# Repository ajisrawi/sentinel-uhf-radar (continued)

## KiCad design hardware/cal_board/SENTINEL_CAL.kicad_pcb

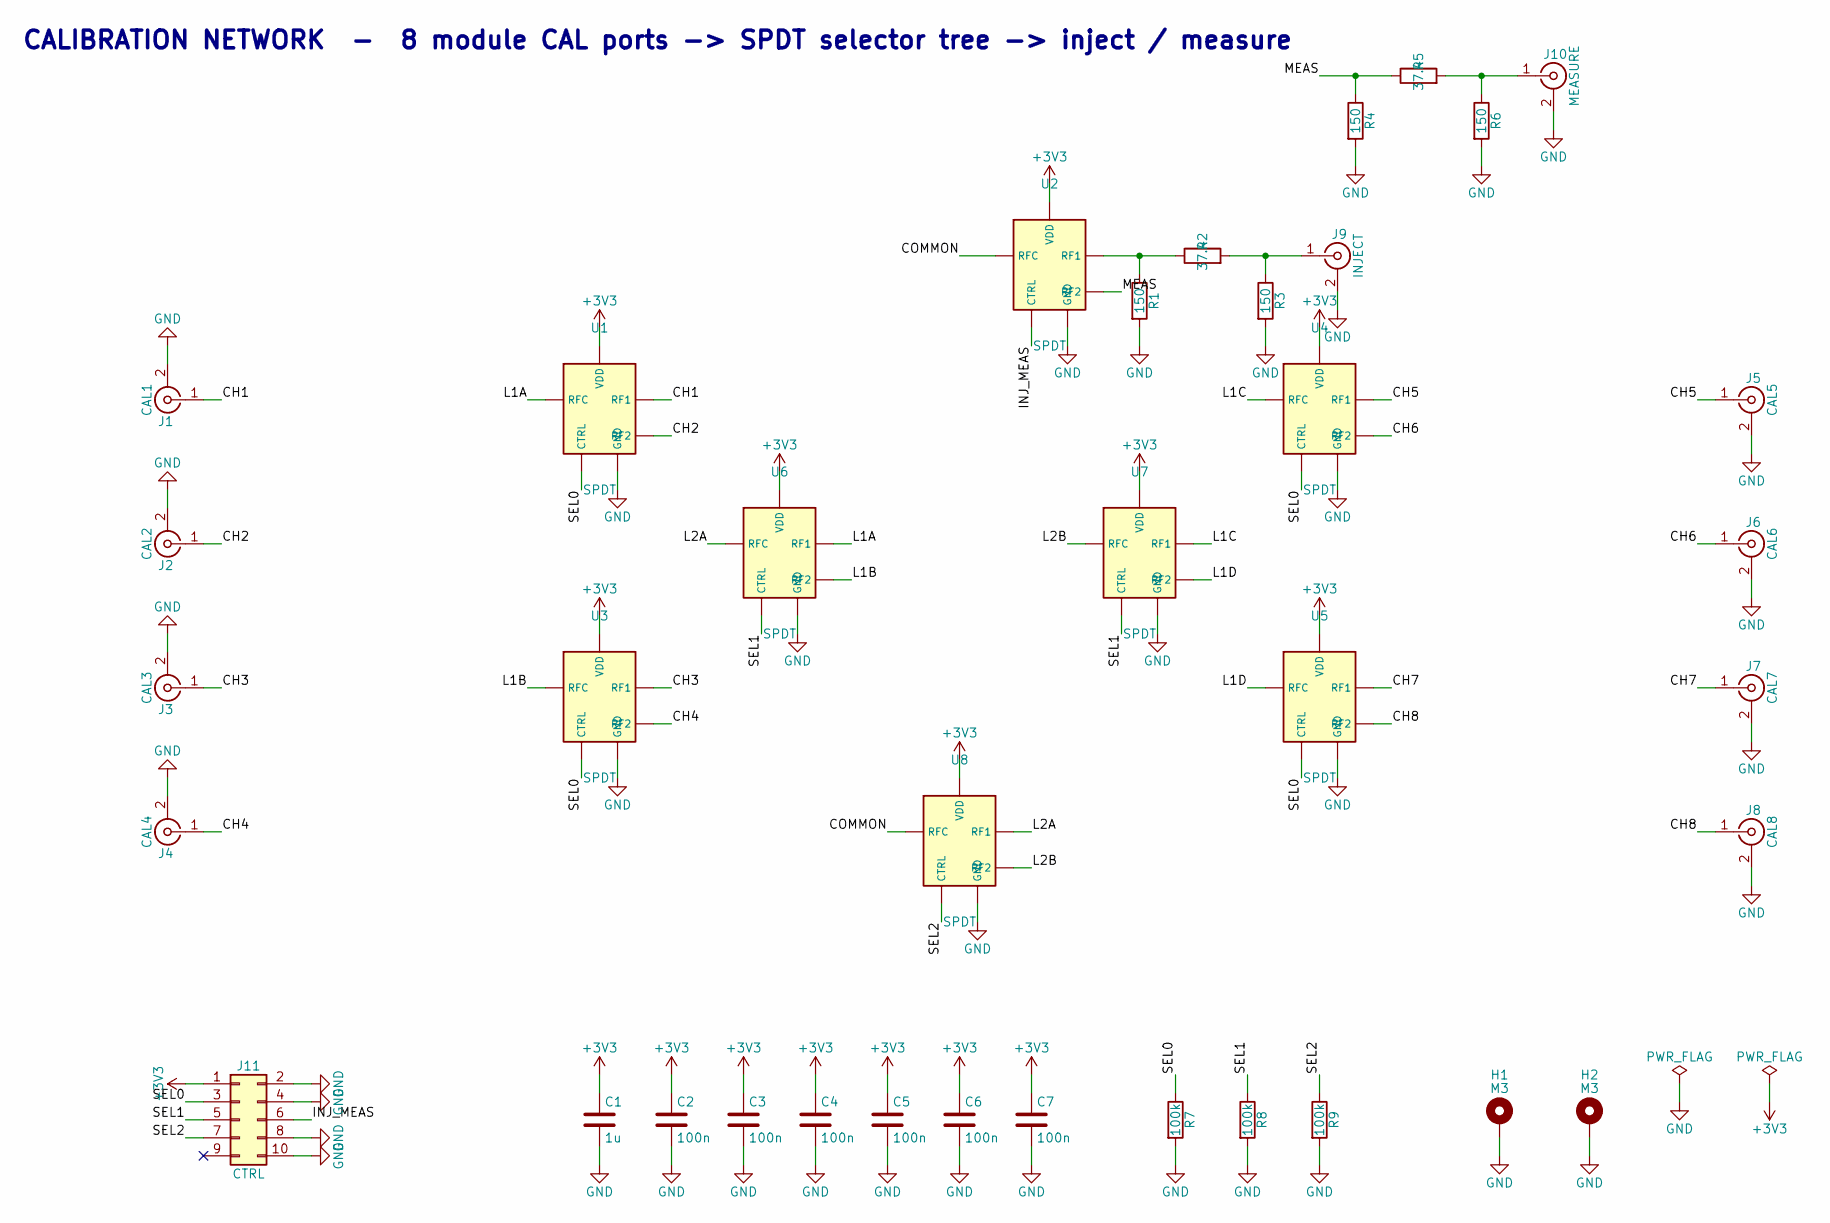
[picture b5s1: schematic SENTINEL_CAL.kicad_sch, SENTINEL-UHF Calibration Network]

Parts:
C1: 1u; C_0603_1608Metric
C2, C3, C4, C5, C6, C7: 100n; C_0603_1608Metric
H1, H2: M3; MountingHole_3.2mm_M3_Pad
J1: CAL1; SMA_Amphenol_132289_EdgeMount
J2: CAL2; SMA_Amphenol_132289_EdgeMount
J3: CAL3; SMA_Amphenol_132289_EdgeMount
J4: CAL4; SMA_Amphenol_132289_EdgeMount
J5: CAL5; SMA_Amphenol_132289_EdgeMount
J6: CAL6; SMA_Amphenol_132289_EdgeMount
J7: CAL7; SMA_Amphenol_132289_EdgeMount
J8: CAL8; SMA_Amphenol_132289_EdgeMount
J9: INJECT; SMA_Amphenol_132289_EdgeMount
J10: MEASURE; SMA_Amphenol_132289_EdgeMount
J11: CTRL; PinHeader_2x05_P2.54mm_Vertical
R1, R3, R4, R6: 150; R_0603_1608Metric
R2, R5: 37.4; R_0603_1608Metric
R7, R8, R9: 100k; R_0603_1608Metric
U1, U2, U3, U4, U5, U6, U7, U8: SPDT; SOT-363_SC-70-6

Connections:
+3V3: C1.1, C2.1, C3.1, C4.1, C5.1, C6.1, C7.1, J11.1, U1.6 (VDD), U2.6 (VDD), U3.6 (VDD), U4.6 (VDD), U5.6 (VDD), U6.6 (VDD), U7.6 (VDD), U8.6 (VDD)
CH1: J1.1 (In), U1.1 (RF1)
CH2: J2.1 (In), U1.3 (RF2)
CH3: J3.1 (In), U3.1 (RF1)
CH4: J4.1 (In), U3.3 (RF2)
CH5: J5.1 (In), U4.1 (RF1)
CH6: J6.1 (In), U4.3 (RF2)
CH7: J7.1 (In), U5.1 (RF1)
CH8: J8.1 (In), U5.3 (RF2)
COMMON: U2.5 (RFC), U8.5 (RFC)
GND: C1.2, C2.2, C3.2, C4.2, C5.2, C6.2, C7.2, H1.1, H2.1, J1.2 (Ext), J2.2 (Ext), J3.2 (Ext), J4.2 (Ext), J5.2 (Ext), J6.2 (Ext), J7.2 (Ext), J8.2 (Ext), J9.2 (Ext), J10.2 (Ext), J11.2, J11.4, J11.8, J11.10, R1.2, R3.2, R4.2, R6.2, R7.2, R8.2, R9.2, U1.2 (GND), U2.2 (GND), U3.2 (GND), U4.2 (GND), U5.2 (GND), U6.2 (GND), U7.2 (GND), U8.2 (GND)
INJ_MEAS: J11.6, U2.4 (CTRL)
L1A: U1.5 (RFC), U6.1 (RF1)
L1B: U3.5 (RFC), U6.3 (RF2)
L1C: U4.5 (RFC), U7.1 (RF1)
L1D: U5.5 (RFC), U7.3 (RF2)
L2A: U6.5 (RFC), U8.1 (RF1)
L2B: U7.5 (RFC), U8.3 (RF2)
MEAS: R4.1, R5.1, U2.3 (RF2)
unnamed: J9.1 (In), R2.2, R3.1
unnamed: J10.1 (In), R5.2, R6.1
unnamed: R1.1, R2.1, U2.1 (RF1)
SEL0: J11.3, R7.1, U1.4 (CTRL), U3.4 (CTRL), U4.4 (CTRL), U5.4 (CTRL)
SEL1: J11.5, R8.1, U6.4 (CTRL), U7.4 (CTRL)
SEL2: J11.7, R9.1, U8.4 (CTRL)

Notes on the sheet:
CALIBRATION NETWORK - 8 module CAL ports -> SPDT selector tree -> inject / measure

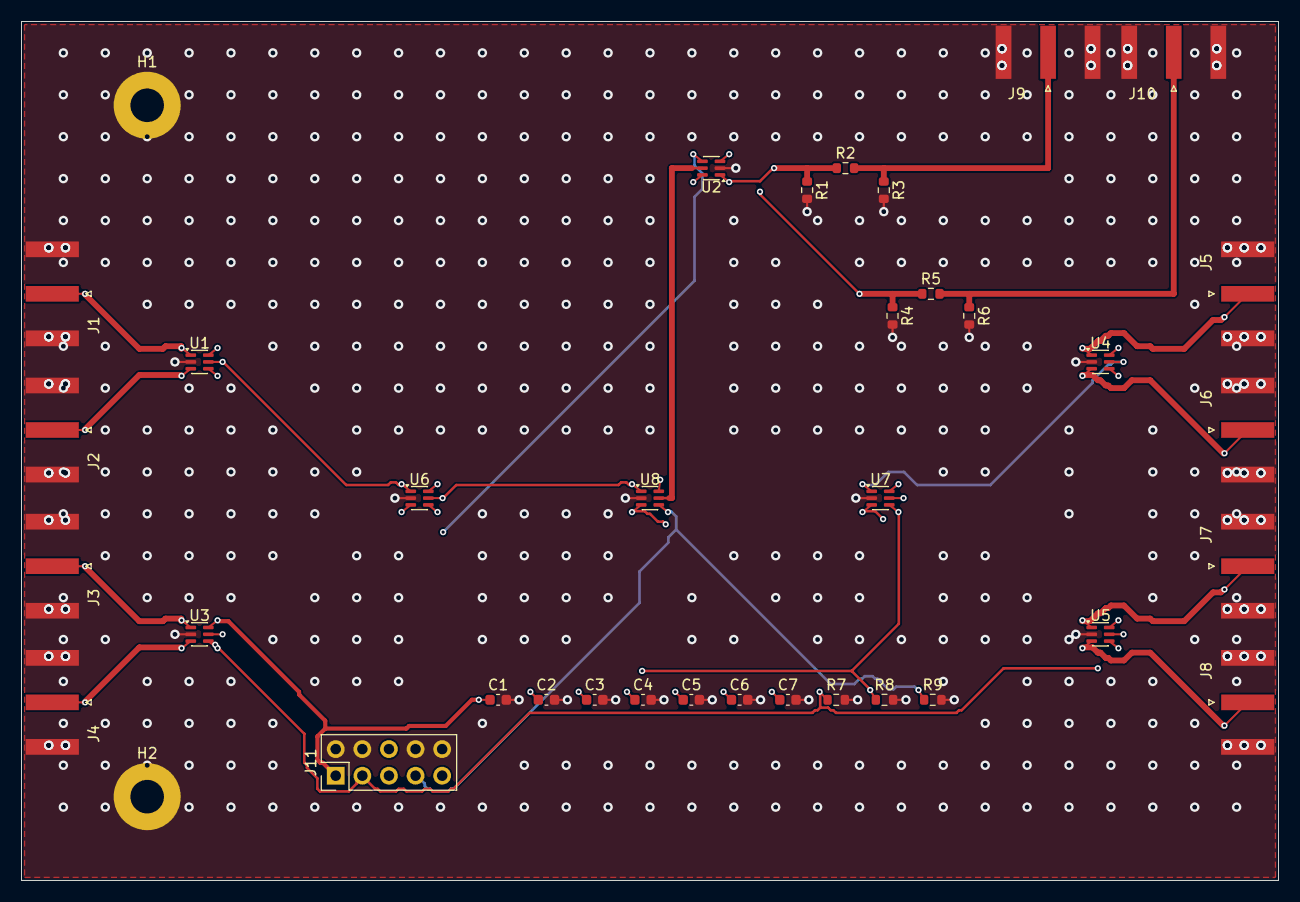
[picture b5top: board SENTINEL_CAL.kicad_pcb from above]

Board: 4 copper layers, 120.0 x 82.0 mm, 37 parts (0 on the bottom side), 25 nets.

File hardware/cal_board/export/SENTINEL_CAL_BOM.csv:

"Item","References","Qty","Value","Footprint","Description","MPN / part class"
"1","C1","1","1u","Capacitor_SMD:C_0603_1608Metric","",""
"2","C2-C7","6","100n","Capacitor_SMD:C_0603_1608Metric","",""
"3","H1,H2","2","M3","MountingHole:MountingHole_3.2mm_M3_Pad","",""
"4","J1","1","CAL1","Connector_Coaxial:SMA_Amphenol_132289_EdgeMount","From T/R module 1 CAL port",""
"5","J2","1","CAL2","Connector_Coaxial:SMA_Amphenol_132289_EdgeMount","From T/R module 2 CAL port",""
"6","J3","1","CAL3","Connector_Coaxial:SMA_Amphenol_132289_EdgeMount","From T/R module 3 CAL port",""
"7","J4","1","CAL4","Connector_Coaxial:SMA_Amphenol_132289_EdgeMount","From T/R module 4 CAL port",""
"8","J5","1","CAL5","Connector_Coaxial:SMA_Amphenol_132289_EdgeMount","From T/R module 5 CAL port",""
"9","J6","1","CAL6","Connector_Coaxial:SMA_Amphenol_132289_EdgeMount","From T/R module 6 CAL port",""
"10","J7","1","CAL7","Connector_Coaxial:SMA_Amphenol_132289_EdgeMount","From T/R module 7 CAL port",""
"11","J8","1","CAL8","Connector_Coaxial:SMA_Amphenol_132289_EdgeMount","From T/R module 8 CAL port",""
"12","J9","1","INJECT","Connector_Coaxial:SMA_Amphenol_132289_EdgeMount","From tile calibration DAC",""
"13","J10","1","MEASURE","Connector_Coaxial:SMA_Amphenol_132289_EdgeMount","To tile calibration ADC",""
"14","J11","1","CTRL","Connector_PinHeader_2.54mm:PinHeader_2x05_P2.54mm_Vertical","Control from RFSoC tile",""
"15","R1,R3,R4,R6","4","150","Resistor_SMD:R_0603_1608Metric","",""
"16","R2,R5","2","37.4","Resistor_SMD:R_0603_1608Metric","6 dB pad",""
"17","R7-R9","3","100k","Resistor_SMD:R_0603_1608Metric","Default channel 1",""
"18","U1-U8","8","SPDT","Package_TO_SOT_SMD:SOT-363_SC-70-6","Inject (RF1) / measure (RF2),Selector tree, SEL0 picks RF1/RF2,Selector tree, SEL1 picks RF1/RF2,Selector tree, SEL2 picks RF1/RF2",""

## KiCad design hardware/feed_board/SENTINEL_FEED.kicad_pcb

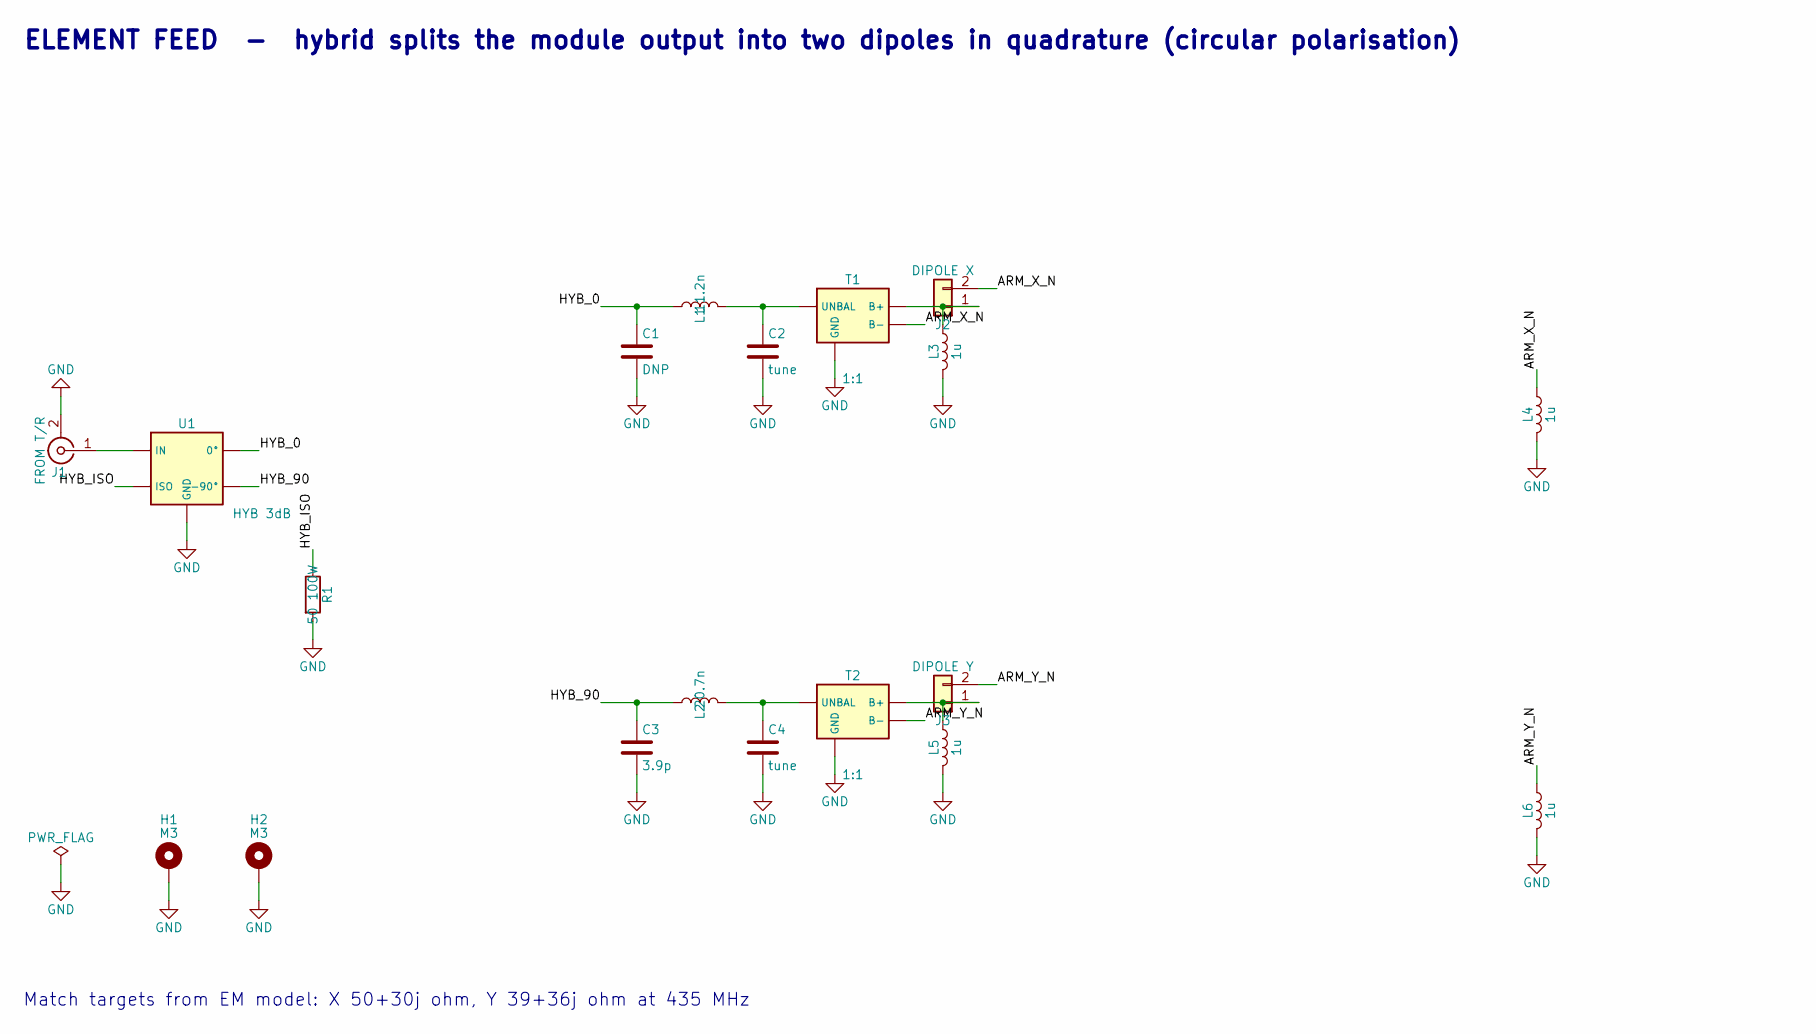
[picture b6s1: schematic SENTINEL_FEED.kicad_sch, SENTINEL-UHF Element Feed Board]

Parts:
C1: DNP; C_2220_5750Metric
C2, C4: tune; C_2220_5750Metric; MPN DNP
C3: 3.9p; C_2220_5750Metric
H1, H2: M3; MountingHole_3.2mm_M3_Pad
J1: FROM T/R; N_EdgeLaunch
J2: DIPOLE X; DipoleArm_M4_Pair
J3: DIPOLE Y; DipoleArm_M4_Pair
L1: 11.2n; L_1210_3225Metric
L2: 20.7n; L_1210_3225Metric
L3, L4, L5, L6: 1u; L_0805_2012Metric
R1: 50 100W; Termination_100W_SMD
T1, T2: 1:1; Balun_SMD_10x8
U1: HYB 3dB; Hybrid90_SMD_15x10

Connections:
ARM_X_N: J2.2, L4.1, T1.4 (B-)
ARM_Y_N: J3.2, L6.1, T2.4 (B-)
GND: C1.2, C2.2, C3.2, C4.2, H1.1, H2.1, J1.2 (Ext), L3.2, L4.2, L5.2, L6.2, R1.2, T1.2 (GND), T2.2 (GND), U1.5 (GND)
HYB_0: C1.1, L1.1, U1.3 (0°)
HYB_90: C3.1, L2.1, U1.4 (-90°)
HYB_ISO: R1.1, U1.2 (ISO)
unnamed: J1.1 (In), U1.1 (IN)
unnamed: J2.1, L3.1, T1.3 (B+)
unnamed: J3.1, L5.1, T2.3 (B+)
unnamed: C2.1, L1.2, T1.1 (UNBAL)
unnamed: C4.1, L2.2, T2.1 (UNBAL)

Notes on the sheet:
ELEMENT FEED - hybrid splits the module output into two dipoles in quadrature (circular polarisation)
Match targets from EM model: X 50+30j ohm, Y 39+36j ohm at 435 MHz

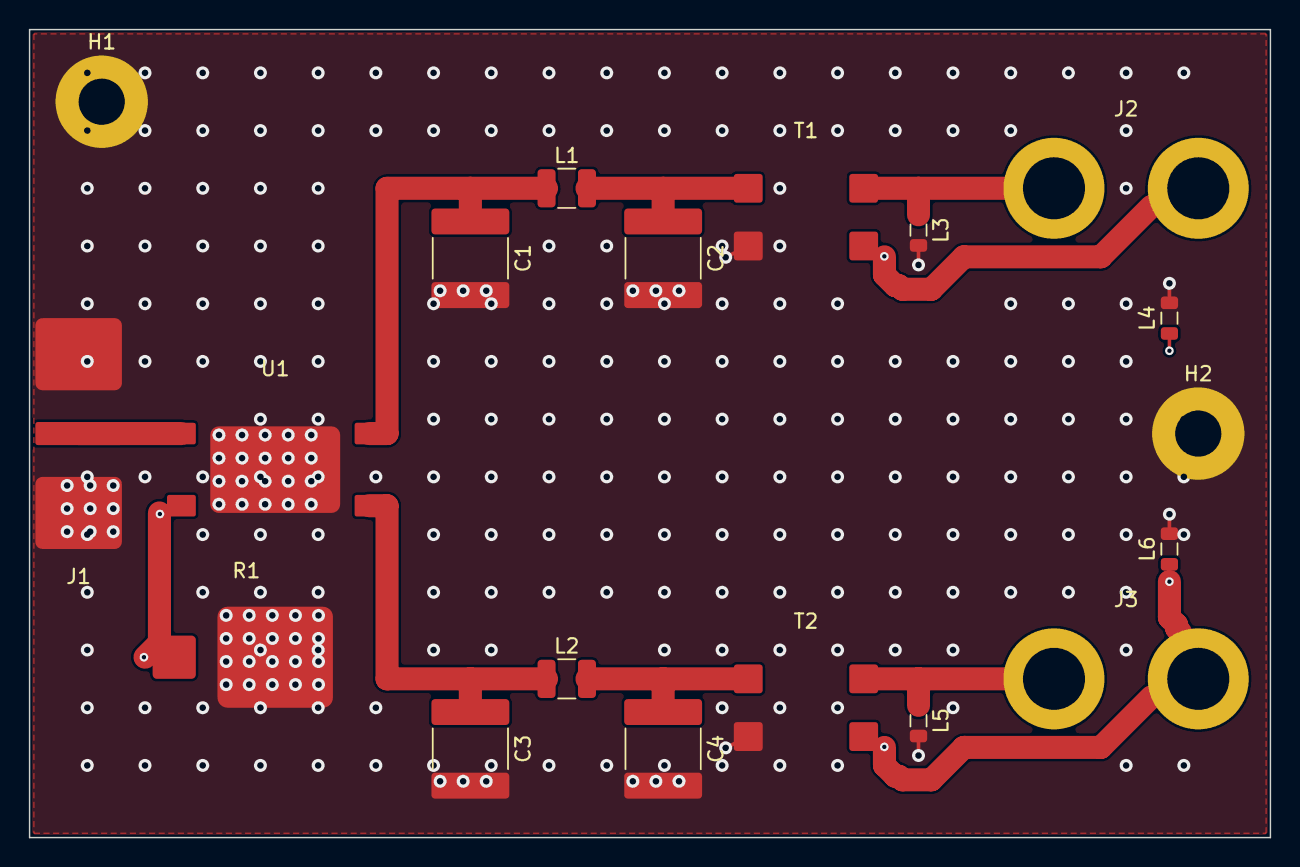
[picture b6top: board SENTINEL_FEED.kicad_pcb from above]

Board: 4 copper layers, 86.0 x 56.0 mm, 19 parts (0 on the bottom side), 11 nets.

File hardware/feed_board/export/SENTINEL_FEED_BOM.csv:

"Item","References","Qty","Value","Footprint","Description","MPN / part class"
"1","C1","1","DNP","Capacitor_SMD:C_2220_5750Metric","X match shunt, 500 V",""
"2","C2,C4","2","tune","Capacitor_SMD:C_2220_5750Metric","Bench trim, fit if needed","DNP"
"3","C3","1","3.9p","Capacitor_SMD:C_2220_5750Metric","Y match shunt, 500 V",""
"4","H1,H2","2","M3","MountingHole:MountingHole_3.2mm_M3_Pad","",""
"5","J1","1","FROM T/R","SENTINEL:N_EdgeLaunch","N-type from T/R module ANT port, 300 W pk",""
"6","J2","1","DIPOLE X","SENTINEL:DipoleArm_M4_Pair","X dipole arms, M4 lugs",""
"7","J3","1","DIPOLE Y","SENTINEL:DipoleArm_M4_Pair","Y dipole arms, M4 lugs",""
"8","L1","1","11.2n","Inductor_SMD:L_1210_3225Metric","X match series",""
"9","L2","1","20.7n","Inductor_SMD:L_1210_3225Metric","Y match series",""
"10","L3-L6","4","1u","Inductor_SMD:L_0805_2012Metric","Static bleed",""
"11","R1","1","50 100W","SENTINEL:Termination_100W_SMD","Isolated-port load, 100 W",""
"12","T1,T2","2","1:1","SENTINEL:Balun_SMD_10x8","1:1 balun, 200 W pk",""
"13","U1","1","HYB 3dB","SENTINEL:Hybrid90_SMD_15x10","3 dB 90 deg hybrid, 420-450 MHz, 500 W",""

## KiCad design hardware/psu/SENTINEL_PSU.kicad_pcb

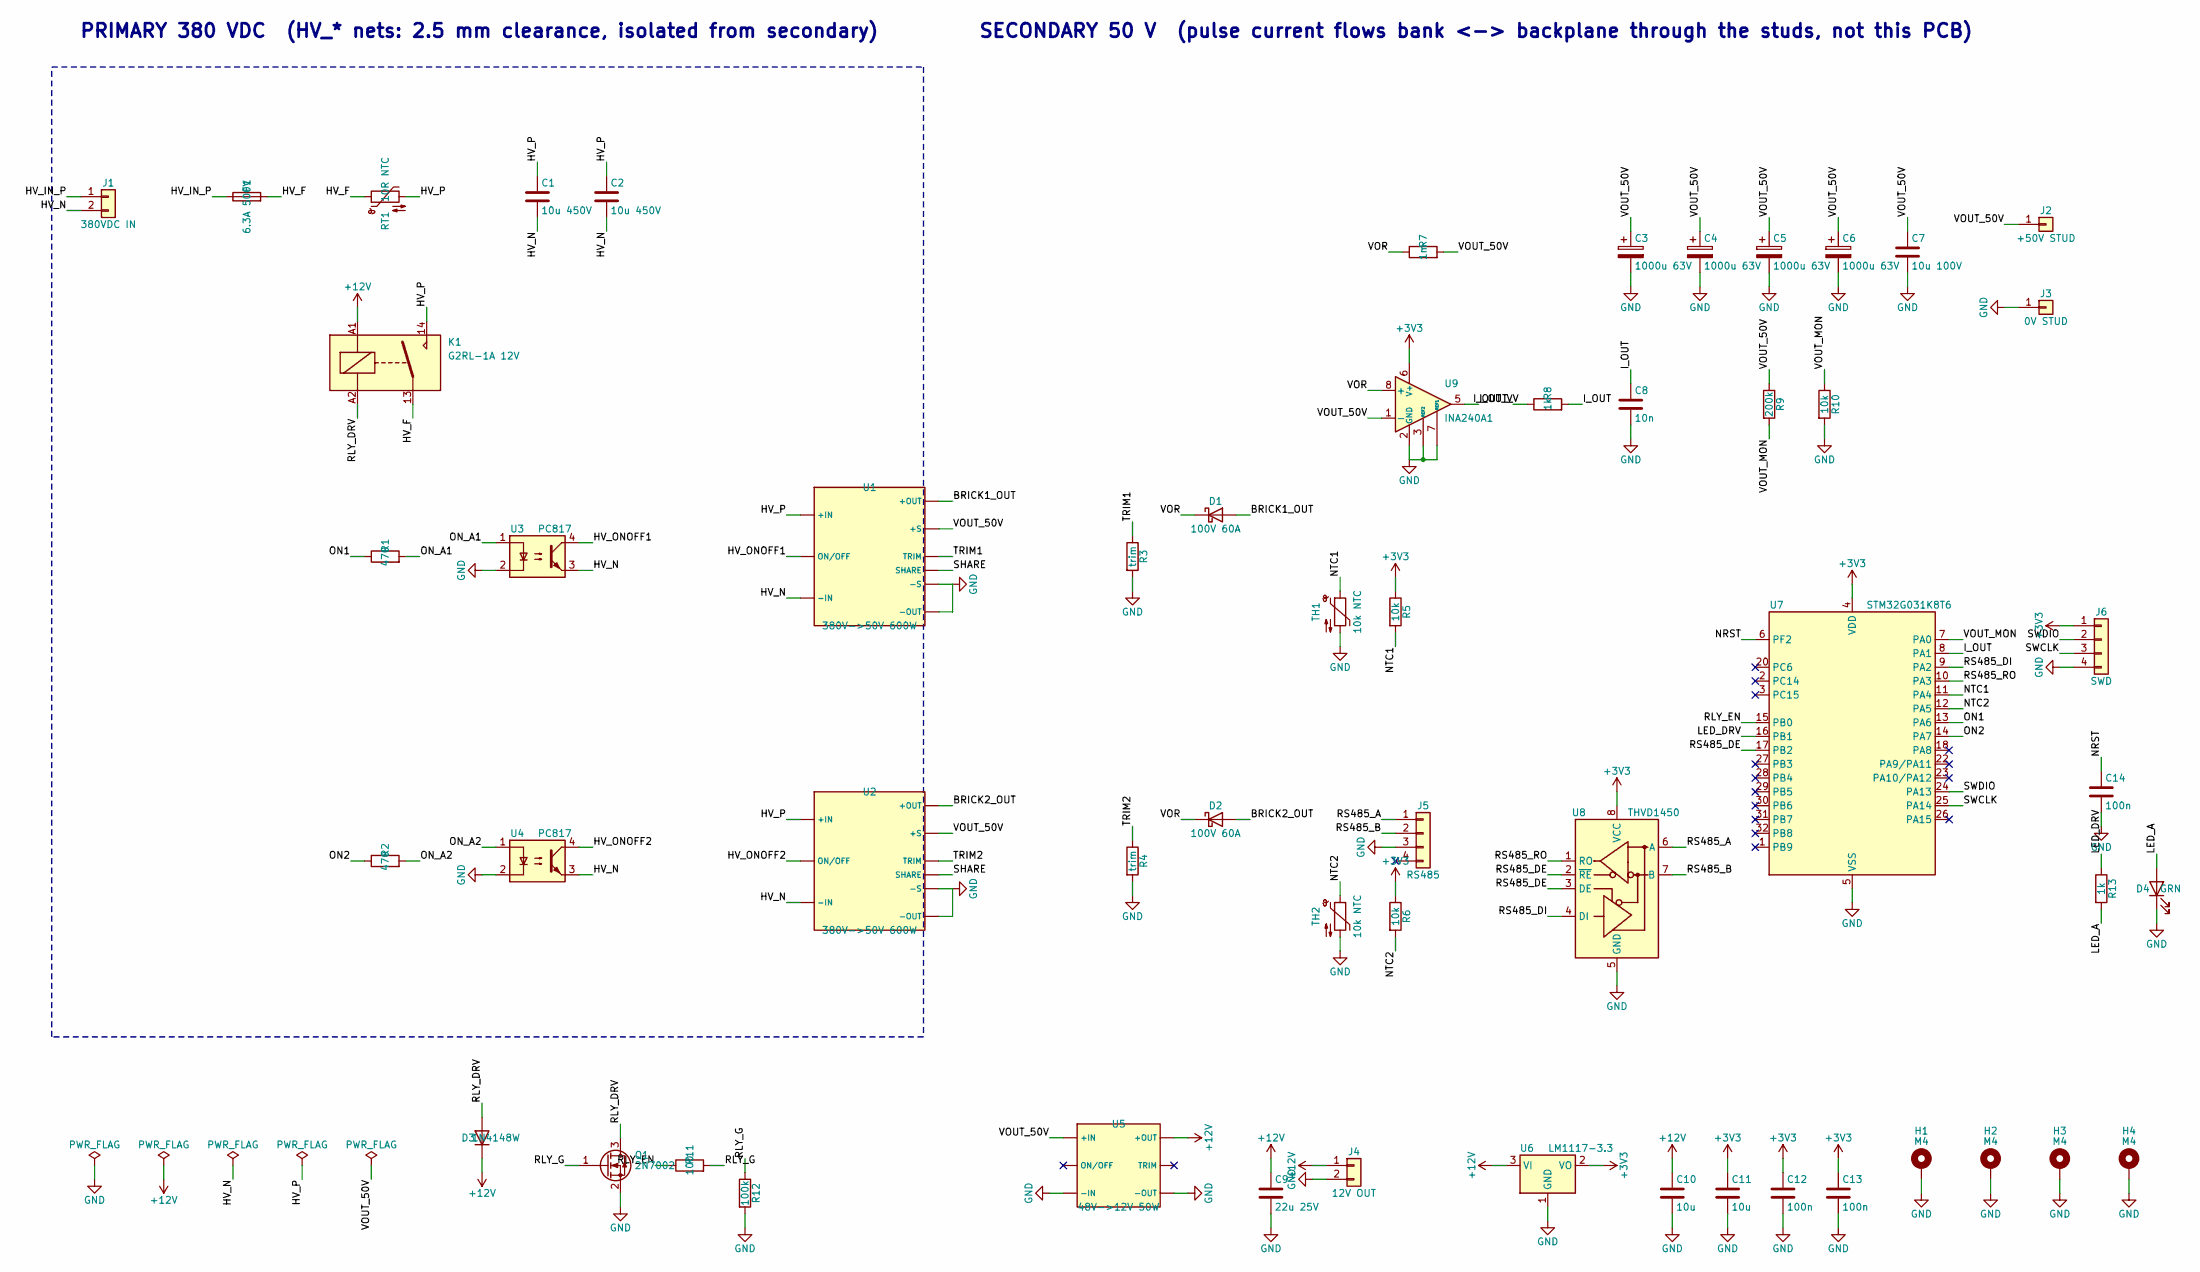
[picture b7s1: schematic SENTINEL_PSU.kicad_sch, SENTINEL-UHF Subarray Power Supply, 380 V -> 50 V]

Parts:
C1, C2: 10u 450V; C_Rect_L26.5mm_W10.5mm_P22.50mm_MKS4
C3, C4, C5, C6: 1000u 63V; CP_Radial_D18.0mm_P7.50mm
C7: 10u 100V; C_1210_3225Metric
C8: 10n; C_0603_1608Metric
C9: 22u 25V; C_1210_3225Metric
C10, C11: 10u; C_1210_3225Metric
C12, C13, C14: 100n; C_0603_1608Metric
D1, D2: 100V 60A; TO-247-2_Vertical
D3: 1N4148W; D_SOD-123
D4: GRN; LED_0603_1608Metric
F1: 6.3A 500V; Fuse_Clips_5x20
H1, H2, H3, H4: M4; MountingHole_3.2mm_M3_Pad
J1: 380VDC IN; Terminal_HV_2P_7.62
J2: +50V STUD; Stud_M6
J3: 0V STUD; Stud_M6
J4: 12V OUT; Molex_Mini-Fit_Jr_5566-02A_2x01_P4.20mm_Vertical
J5: RS485; PinHeader_1x04_P2.54mm_Vertical
J6: SWD; PinHeader_1x04_P2.54mm_Vertical
K1: G2RL-1A 12V; Relay_SPST_Omron_G2RL-1A
Q1: 2N7002; SOT-23
R1, R2: 470; R_0603_1608Metric
R3, R4: trim; R_0603_1608Metric; MPN value per brick datasheet
R5, R6, R10: 10k; R_0603_1608Metric
R7: 1m; R_2512_6332Metric
R8, R13: 1k; R_0603_1608Metric
R9: 200k; R_0603_1608Metric
R11: 100; R_0603_1608Metric
R12: 100k; R_0603_1608Metric
RT1: 10R NTC; NTC_Disc_D15_P7.5
TH1, TH2: 10k NTC; R_0603_1608Metric
U1, U2: 380V->50V 600W; Brick_Full_THT
U3, U4: PC817; SMDIP-4_W7.62mm
U5: 48V->12V 50W; Brick_16_THT
U6: LM1117-3.3; TO-252-3_TabPin2
U7: STM32G031K8T6; LQFP-32_7x7mm_P0.8mm
U8: THVD1450; SOIC-8_3.9x4.9mm_P1.27mm
U9: INA240A1; SOIC-8_3.9x4.9mm_P1.27mm

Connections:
+3V3: C11.1, C12.1, C13.1, J6.1, R5.1, R6.1, U6.2 (VO), U7.4 (VDD), U8.8 (VCC), U9.6 (V+)
+12V: C9.1, C10.1, D3.1 (K), J4.1, K1.A1, U5.6 (+OUT), U6.3 (VI)
BRICK1_OUT: D1.2 (A), U1.8 (+OUT)
BRICK2_OUT: D2.2 (A), U2.8 (+OUT)
GND: C3.2, C4.2, C5.2, C6.2, C7.2, C8.2, C9.2, C10.2, C11.2, C12.2, C13.2, C14.2, D4.1 (K), H1.1, H2.1, H3.1, H4.1, J3.1, J4.2, J5.3, J6.4, Q1.2 (S), R3.2, R4.2, R10.2, R12.2, TH1.2, TH2.2, U1.4 (-OUT), U1.5 (-S), U2.4 (-OUT), U2.5 (-S), U3.2, U4.2, U5.3 (-IN), U5.4 (-OUT), U6.1 (GND), U7.5 (VSS), U8.5 (GND), U9.2 (GND), U9.3 (REF2), U9.4 (GND), U9.7 (REF1)
HV_F: F1.2, K1.13, RT1.1
HV_IN_P: F1.1, J1.1
HV_N: C1.2, C2.2, J1.2, U1.3 (-IN), U2.3 (-IN), U3.3, U4.3
HV_ONOFF1: U1.2 (ON/OFF), U3.4
HV_ONOFF2: U2.2 (ON/OFF), U4.4
HV_P: C1.1, C2.1, K1.14, RT1.2, U1.1 (+IN), U2.1 (+IN)
I_OUT: C8.1, R8.2, U7.8 (PA1)
I_OUT_V: R8.1, U9.5
LED_A: D4.2 (A), R13.2
LED_DRV: R13.1, U7.16 (PB1)
NRST: C14.1, U7.6 (PF2)
NTC1: R5.2, TH1.1, U7.11 (PA4)
NTC2: R6.2, TH2.1, U7.12 (PA5)
ON1: R1.1, U7.13 (PA6)
ON2: R2.1, U7.14 (PA7)
ON_A1: R1.2, U3.1
ON_A2: R2.2, U4.1
RLY_DRV: D3.2 (A), K1.A2, Q1.3 (D)
RLY_EN: R11.1, U7.15 (PB0)
RLY_G: Q1.1 (G), R11.2, R12.1
RS485_A: J5.1, U8.6 (A)
RS485_B: J5.2, U8.7 (B)
RS485_DE: U7.17 (PB2), U8.2 (~RE), U8.3 (DE)
RS485_DI: U7.9 (PA2), U8.4 (DI)
RS485_RO: U7.10 (PA3), U8.1 (RO)
SHARE: U1.9 (SHARE), U2.9 (SHARE)
SWCLK: J6.3, U7.25 (PA14)
SWDIO: J6.2, U7.24 (PA13)
TRIM1: R3.1, U1.6 (TRIM)
TRIM2: R4.1, U2.6 (TRIM)
VOR: D1.1 (K), D2.1 (K), R7.1, U9.8 (+)
VOUT_50V: C3.1, C4.1, C5.1, C6.1, C7.1, J2.1, R7.2, R9.1, U1.7 (+S), U2.7 (+S), U5.1 (+IN), U9.1 (-)
VOUT_MON: R9.2, R10.1, U7.7 (PA0)

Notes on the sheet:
PRIMARY 380 VDC (HV_* nets: 2.5 mm clearance, isolated from secondary)
SECONDARY 50 V (pulse current flows bank <-> backplane through the studs, not this PCB)

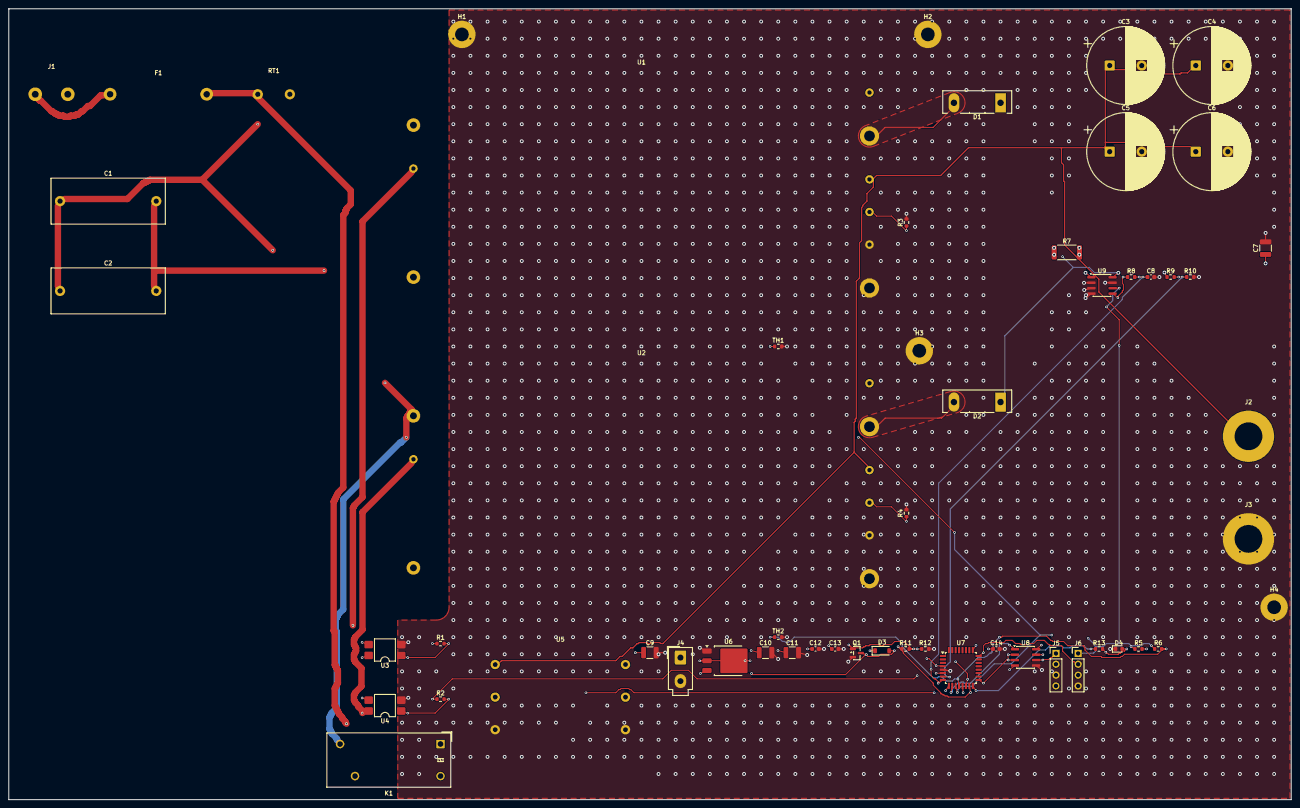
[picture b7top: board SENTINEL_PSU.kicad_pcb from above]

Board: 4 copper layers, 300.0 x 185.0 mm, 56 parts (0 on the bottom side), 38 nets.

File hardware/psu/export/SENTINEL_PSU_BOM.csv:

"Item","References","Qty","Value","Footprint","Description","MPN / part class"
"1","C1,C2","2","10u 450V","Capacitor_THT:C_Rect_L26.5mm_W10.5mm_P22.50mm_MKS4","Input film capacitor",""
"2","C3-C6","4","1000u 63V","Capacitor_THT:CP_Radial_D18.0mm_P7.50mm","Output bulk",""
"3","C7","1","10u 100V","Capacitor_SMD:C_1210_3225Metric","",""
"4","C8","1","10n","Capacitor_SMD:C_0603_1608Metric","",""
"5","C9","1","22u 25V","Capacitor_SMD:C_1210_3225Metric","",""
"6","C10,C11","2","10u","Capacitor_SMD:C_1210_3225Metric","",""
"7","C12-C14","3","100n","Capacitor_SMD:C_0603_1608Metric","",""
"8","D1,D2","2","100V 60A","Package_TO_SOT_THT:TO-247-2_Vertical","Output OR-ing diode",""
"9","D3","1","1N4148W","Diode_SMD:D_SOD-123","Relay flyback",""
"10","D4","1","GRN","LED_SMD:LED_0603_1608Metric","",""
"11","F1","1","6.3A 500V","SENTINEL:Fuse_Clips_5x20","Input fuse, 500 VDC rated",""
"12","H1-H4","4","M4","MountingHole:MountingHole_3.2mm_M3_Pad","",""
"13","J1","1","380VDC IN","SENTINEL:Terminal_HV_2P_7.62","380 VDC site distribution bus",""
"14","J2","1","+50V STUD","SENTINEL:Stud_M6","M6 stud: capacitor bank + and backplane 50 V",""
"15","J3","1","0V STUD","SENTINEL:Stud_M6","M6 stud: return",""
"16","J4","1","12V OUT","Connector_Molex:Molex_Mini-Fit_Jr_5566-02A_2x01_P4.20mm_Vertical","12 V aux to backplane",""
"17","J5","1","RS485","Connector_PinHeader_2.54mm:PinHeader_1x04_P2.54mm_Vertical","Telemetry to tile controller",""
"18","J6","1","SWD","Connector_PinHeader_2.54mm:PinHeader_1x04_P2.54mm_Vertical","",""
"19","K1","1","G2RL-1A 12V","Relay_THT:Relay_SPST_Omron_G2RL-1A","Inrush bypass relay, 5 kV coil-contact",""
"20","Q1","1","2N7002","Package_TO_SOT_SMD:SOT-23","",""
"21","R1,R2","2","470","Resistor_SMD:R_0603_1608Metric","",""
"22","R3,R4","2","trim","Resistor_SMD:R_0603_1608Metric","Trim-up to 50.0 V per vendor formula","value per brick datasheet"
"23","R5,R6,R10","3","10k","Resistor_SMD:R_0603_1608Metric","",""
"24","R7","1","1m","Resistor_SMD:R_2512_6332Metric","Brick current shunt",""
"25","R8,R13","2","1k","Resistor_SMD:R_0603_1608Metric","",""
"26","R9","1","200k","Resistor_SMD:R_0603_1608Metric","",""
"27","R11","1","100","Resistor_SMD:R_0603_1608Metric","",""
"28","R12","1","100k","Resistor_SMD:R_0603_1608Metric","",""
"29","RT1","1","10R NTC","SENTINEL:NTC_Disc_D15_P7.5","Inrush limiter, bypassed by K1 after precharge",""
"30","TH1,TH2","2","10k NTC","Resistor_SMD:R_0603_1608Metric","Brick 1 baseplate temperature,Brick 2 baseplate temperature",""
"31","U1,U2","2","380V->50V 600W","SENTINEL:Brick_Full_THT","Isolated full brick, 380 V in, 50 V / 12 A out, current share",""
"32","U3,U4","2","PC817","Package_DIP:SMDIP-4_W7.62mm","Brick enable across the isolation barrier",""
"33","U5","1","48V->12V 50W","SENTINEL:Brick_16_THT","12 V aux for modules and relay",""
"34","U6","1","LM1117-3.3","Package_TO_SOT_SMD:TO-252-3_TabPin2","",""
"35","U7","1","STM32G031K8T6","Package_QFP:LQFP-32_7x7mm_P0.8mm","Supervisor: soft start, OV/UV, current, temperature, telemetry",""
"36","U8","1","THVD1450","Package_SO:SOIC-8_3.9x4.9mm_P1.27mm","",""
"37","U9","1","INA240A1","Package_SO:SOIC-8_3.9x4.9mm_P1.27mm","",""

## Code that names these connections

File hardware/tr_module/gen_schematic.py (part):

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    sch.text("RX CHAIN  -  limiter protected, NF 1.1 dB, G 34 dB", 25, 145, 3.0)
    sch.rect(20, 150, 445, 215)
    r = Chain(sch, 35.56, 175.26)
    r.start_label("RX_CIRC")
    r.shunt([P("D1", "Device:D", "PIN", DSMB, rot=90, Description="Coarse PIN limiter diode, 100 W pk")], "GND")
    r.shunt([P("L8", L, "100n", L0603, Description="Limiter DC return")], "GND")
    r.series(P("C23", C, "100p", C0603, rot=90), "1", "2")
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    sch.text("POWER MONITOR AND CALIBRATION PORT", 25, 228, 3.0)
    sch.rect(20, 233, 445, 330)
    d = Chain(sch, 35.56, 256.54)
    d.start_label("CPL_FWD")
    d.shunt([P("R12", R, "96", R0603)], "GND")
    d.series(P("R13", R, "71", R0603, rot=90, Description="10 dB pi pad"), "1", "2")
    d.shunt([P("R14", R, "96", R0603)], "GND")
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    d.series(P("C27", C, "100p", C0603, rot=90), "1", "2")
    d.series(P("U6", "SENTINEL:LogDet", "DET FWD", SOT23_6, nets={"5": "+5V", "3": "+5V", "2": "GND", "6": "GND"},
               Description="Forward power detector"), "1", "4")
    d.end_label("V_FWD")

    e = Chain(sch, 35.56, 292.1)
    e.start_label("CPL_REV")
    e.shunt([P("R15", R, "96", R0603)], "GND")
    e.series(P("R16", R, "71", R0603, rot=90), "1", "2")
    e.shunt([P("R17", R, "96", R0603)], "GND")
    e.series(P("C28", C, "100p", C0603, rot=90), "1", "2")
    e.series(P("U7", "SENTINEL:LogDet", "DET REV", SOT23_6, nets={"5": "+5V", "3": "+5V", "2": "GND", "6": "GND"},
               Description="Reflected power detector (VSWR trip)"), "1", "4")
    e.end_label("V_REFL")

    k = Chain(sch, 220.98, 256.54)
    k.start_label("CAL_PORT")
    k.series(P("C29", C, "100p", C0603, rot=90), "1", "2")
    k.end(P("J4", COAX, "CAL", SMA, nets={"2": "GND"},
            Description="SMA to array calibration network (mutual-coupling cal)"), "1")
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    sch.add("J5", "Connector_Generic:Conn_02x08_Odd_Even", "BACKPLANE", HDR2x8, 711.2, 101.6, 0,
            {"1": "+12V", "3": "+12V", "5": "RS485_A", "7": "RS485_B", "9": "TX_EN", "11": "FAULT_N",
             "13": "NC", "15": "NC", **{str(n): "GND" for n in range(2, 17, 2)}},
            Description="Tile backplane: aux power, RS-485, TX_EN gate, fault; even pins ground")
    sch.pwr_flag("GND", 762, 66.04)
    sch.pwr_flag("+12V", 777.24, 66.04)
    sch.pwr_flag("+5V", 792.48, 66.04)
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
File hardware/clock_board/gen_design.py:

"""
SENTINEL-UHF clock and timing distribution board (one per 8 tiles).

10 MHz + 1 PPS from the site GPS-disciplined rubidium master come in on SMA.
A narrow-loop integer-N PLL locks a 122.88 MHz VCXO to the 10 MHz (jitter
cleaning: the VCXO sets close-in phase noise, the loop only removes drift).
SYSREF for deterministic multi-tile sync is the PPS re-timed by the clean
clock in a D flip-flop, so it is phase aligned to the sample clock on every
tile. Six quad LVDS drivers send CLK, SYSREF and PPS to 8 RFSoC tiles.

The PLL is a generic integer-N PLL in TSSOP-16 (ADF4002 class); its pin map
must be checked against the selected part's datasheet before layout release.
"""
import sys
from pathlib import Path

HERE = Path(__file__).parent
sys.path.insert(0, str(HERE.parent / "tools"))
from schgen import Schematic, custom_symbol, g_rect, write_project  # noqa: E402

PRO = "SENTINEL_CLOCK"
R0603, C0603 = "Resistor_SMD:R_0603_1608Metric", "Capacitor_SMD:C_0603_1608Metric"
SMA = "Connector_Coaxial:SMA_Amphenol_132289_EdgeMount"
SOIC16, TSSOP16 = "Package_SO:SOIC-16_3.9x9.9mm_P1.27mm", "Package_SO:TSSOP-16_4.4x5mm_P0.65mm"
SOT23_5, SC70_6, SOIC8 = "Package_TO_SOT_SMD:SOT-23-5", "Package_TO_SOT_SMD:SOT-363_SC-70-6", "Package_SO:SOIC-8_3.9x4.9mm_P1.27mm"
HDR2x5 = "Connector_PinHeader_2.54mm:PinHeader_2x05_P2.54mm_Vertical"
HDR1x4 = "Connector_PinHeader_2.54mm:PinHeader_1x04_P2.54mm_Vertical"
VCXO_FP = "Oscillator:Oscillator_SMD_EuroQuartz_XO53-4Pin_5.0x3.2mm"

PLL_PINS = [(1, "RSET"), (2, "CP"), (3, "CPGND"), (4, "AGND"), (5, "RFINB"), (6, "RFINA"), (7, "AVDD"), (8, "REFIN"),
            (9, "DGND"), (10, "CE"), (11, "CLK"), (12, "DATA"), (13, "LE"), (14, "MUXOUT"), (15, "DVDD"), (16, "VP")]
CUSTOM = [
    custom_symbol("PLL_IntN", "U", "PLL_IntN", TSSOP16, "Integer-N PLL, 200 MHz RF in, SPI (ADF4002 class)",
                  [(n, nm, -12.7 if i < 8 else 12.7, 8.89 - 2.54 * (i % 8), 0 if i < 8 else 180, 2.54)
                   for i, (n, nm) in enumerate(PLL_PINS)], [g_rect(-10.16, 11.43, 10.16, -11.43)]),
    custom_symbol("VCXO", "Y", "VCXO", VCXO_FP, "VCXO 122.88 MHz, LVCMOS, +/-50 ppm pull",
                  [(1, "VC", -7.62, 0, 0, 2.54), (2, "GND", 0, -7.62, 90, 2.54), (3, "OUT", 7.62, 0, 180, 2.54),
                   (4, "VDD", 0, 7.62, 270, 2.54)], [g_rect(-5.08, 5.08, 5.08, -5.08)]),
]


def build():
    sch = Schematic(PRO, "SENTINEL-UHF Clock & Timing Distribution (8 tiles)", "A2", CUSTOM)
    sch.text("CLOCK  -  10 MHz -> PLL + 122.88 MHz VCXO -> LVDS to 8 tiles; SYSREF = PPS re-timed by CLK", 20, 22, 2.5)
    sch.add("J1", "Connector:Conn_Coaxial", "10MHz IN", SMA, 30.48, 60.96, 180, {"1": "REF10", "2": "GND"},
            Description="10 MHz from site master, +7 dBm sine")
    sch.add("R1", "Device:R", "51", R0603, 45.72, 71.12, 0, {"1": "REF10", "2": "GND"}, Description="50 ohm termination")
    sch.add("C1", "Device:C", "100n", C0603, 55.88, 60.96, 90, {"1": "REF10", "2": "REFIN"})
    sch.add("J2", "Connector:Conn_Coaxial", "PPS IN", SMA, 30.48, 111.76, 180, {"1": "PPS_RAW", "2": "GND"},
            Description="1 PPS from site master")
    sch.add("R2", "Device:R", "51", R0603, 45.72, 121.92, 0, {"1": "PPS_RAW", "2": "GND"})
    sch.add("U2", "74xGxx:74LVC1G17", "74LVC1G17", SOT23_5, 71.12, 111.76, 0,
            {"2": "PPS_RAW", "4": "PPS", "3": "GND", "5": "+3V3"}, Description="PPS Schmitt buffer")
    pll = {"1": "RSET", "2": "CP", "3": "GND", "4": "GND", "5": "RFINB", "6": "RFIN", "7": "+3V3A", "8": "REFIN",
           "9": "GND", "10": "PLL_CE", "11": "SPI_SCK", "12": "SPI_MOSI", "13": "PLL_LE", "14": "LOCK",
           "15": "+3V3A", "16": "+3V3A"}
    sch.add("U1", "SENTINEL:PLL_IntN", "PLL", TSSOP16, 104.14, 76.2, 0, pll, Description="Integer-N PLL, verify pin map")
    for ref, val, n1, n2, x, y in (("R3", "5.1k", "RSET", "GND", 81.28, 99.06), ("C4", "2.2n", "CP", "GND", 137.16, 99.06),
                                   ("R4", "3.3k", "CP", "LF_Z", 147.32, 99.06), ("C5", "22n", "LF_Z", "GND", 157.48, 99.06),
                                   ("R5", "6.8k", "CP", "VC", 167.64, 99.06), ("C6", "1n", "VC", "GND", 177.8, 99.06),
                                   ("C7", "100p", "CLK_RAW", "RFIN", 187.96, 99.06), ("C8", "100p", "RFINB", "GND", 198.12, 99.06)):
        sch.add(ref, "Device:C" if ref[0] == "C" else "Device:R", val, C0603 if ref[0] == "C" else R0603, x, y, 0,
                {"1": n1, "2": n2}, Description="Loop filter (100 Hz loop)" if ref in ("C4", "R4", "C5", "R5", "C6") else "")
    sch.add("Y1", "SENTINEL:VCXO", "122.88MHz", VCXO_FP, 162.56, 66.04, 0,
            {"1": "VC", "2": "GND", "3": "CLK_RAW", "4": "+3V3A"}, Description="122.88 MHz VCXO, low phase noise")
    sch.add("R6", "Device:R", "33", R0603, 187.96, 66.04, 90, {"1": "CLK_RAW", "2": "CLK"}, Description="Source termination")
    sch.add("U3", "74xGxx:74LVC1G175", "74LVC1G175", SC70_6, 104.14, 137.16, 0,
            {"1": "CLK", "3": "PPS", "4": "SYSREF_RAW", "6": "+3V3", "5": "+3V3", "2": "GND"},
            Description="SYSREF: PPS re-timed by CLK")
    sch.add("R7", "Device:R", "33", R0603, 132.08, 132.08, 90, {"1": "SYSREF_RAW", "2": "SYSREF"})
    # LVDS drivers and tile connectors
    groups = (("CLK", "CLK"), ("SYSREF", "SYS"), ("PPS", "PPS"))
    u = 4
    for gi, (src, tag) in enumerate(groups):
        for half in range(2):
            nets = {"1": "LVDS_EN", "8": "GND", "4": "+3V3", "5": "GND"}
            for k, (din, pp, pn) in enumerate((("2", "15", "16"), ("3", "14", "13"), ("6", "11", "12"), ("7", "10", "9"))):
                t = 4 * half + k + 1
                nets.update({din: src, pp: f"{tag}_P{t}", pn: f"{tag}_N{t}"})
            sch.add(f"U{u}", "Interface:SN65LVDS047D", "SN65LVDS047", SOIC16, 241.3 + 50.8 * gi, 60.96 + 76.2 * half, 0, nets,
                    Description=f"Quad LVDS driver, {src} to tiles {4 * half + 1}-{4 * half + 4}")
            u += 1
    for t in range(1, 9):
        sch.add(f"J{2 + t}", "Connector_Generic:Conn_02x05_Odd_Even", f"TILE{t}", HDR2x5, 406.4, 30.48 + 25.4 * (t - 1), 0,
                {"1": f"CLK_P{t}", "2": f"CLK_N{t}", "3": "GND", "4": "GND", "5": f"SYS_P{t}", "6": f"SYS_N{t}",
                 "7": "GND", "8": "GND", "9": f"PPS_P{t}", "10": f"PPS_N{t}"}, Description=f"Clock bundle to tile {t}")
    # controller
    sch.add("U10", "MCU_ST_STM32G031:STM32G031K8Tx" if False else "MCU_ST_STM32G0:STM32G031K8Tx", "STM32G031K8T6",
            "Package_QFP:LQFP-32_7x7mm_P0.8mm", 104.14, 210.82, 0, {
                "4": "+3V3", "5": "GND", "6": "NRST", "7": "LOCK", "8": "LVDS_EN", "9": "RS485_DI", "10": "RS485_RO",
                "11": "PLL_LE", "12": "SPI_SCK", "13": "PLL_CE", "14": "SPI_MOSI", "15": "LED_LOCK", "18": "RS485_DE",
                "24": "SWDIO", "25": "SWCLK", **{str(n): "NC" for n in (1, 2, 3, 16, 17, 20, 22, 23, 26, 27, 28, 29, 30, 31, 32)}},
            Description="Programs the PLL, reports lock, enables outputs")
    sch.add("U11", "Interface_UART:THVD1450D", "THVD1450", SOIC8, 162.56, 215.9, 0,
            {"1": "RS485_RO", "2": "RS485_DE", "3": "RS485_DE", "4": "RS485_DI", "5": "GND", "6": "RS485_A",
             "7": "RS485_B", "8": "+3V3"})
    sch.add("J11", "Connector_Generic:Conn_01x04", "RS485", HDR1x4, 198.12, 210.82, 0,
            {"1": "RS485_A", "2": "RS485_B", "3": "GND", "4": "NC"}, Description="To site timing controller")
    sch.add("J12", "Connector_Generic:Conn_01x04", "SWD", HDR1x4, 50.8, 200.66, 0,
            {"1": "+3V3", "2": "SWDIO", "3": "SWCLK", "4": "GND"})
    sch.add("J13", "Connector_Generic:Conn_01x02", "5V IN", "Connector_Molex:Molex_Mini-Fit_Jr_5566-02A_2x01_P4.20mm_Vertical",
            241.3, 228.6, 0, {"1": "+5V", "2": "GND"})
    for i, (ref, out) in enumerate((("U12", "+3V3"), ("U13", "+3V3A"))):
        sch.add(ref, "Regulator_Linear:AP2112K-3.3", "AP2112K-3.3", SOT23_5, 279.4 + 45.72 * i, 228.6, 0,
                {"1": "+5V", "3": "+5V", "2": "GND", "5": out}, Description="Analog rail for PLL/VCXO" if i else "")
    sch.add("R8", "Device:R", "1k", R0603, 50.8, 228.6, 0, {"1": "LED_LOCK", "2": "LED_A"})
    sch.add("D1", "Device:LED", "LOCK", "LED_SMD:LED_0603_1608Metric", 60.96, 228.6, 90, {"2": "LED_A", "1": "GND"})
    caps = [("1u", "+5V"), ("1u", "+3V3"), ("1u", "+5V"), ("1u", "+3V3A")] + [("100n", "+3V3")] * 9 + [("100n", "+3V3A")] * 3
    for i, (val, n1) in enumerate(caps):
        sch.add(f"C{9 + i}", "Device:C", val, C0603, 241.3 + 10.16 * (i % 12), 251.46 + 22.86 * (i // 12), 0,
                {"1": n1, "2": "GND"})
    sch.add("C25", "Device:C", "100n", C0603, 81.28, 236.22, 0, {"1": "NRST", "2": "GND"})
    for i in range(4):
        sch.add(f"H{i + 1}", "Mechanical:MountingHole_Pad", "M3", "MountingHole:MountingHole_3.2mm_M3_Pad",
                355.6 + 12.7 * i, 254.0, 0, {"1": "GND"})
    sch.pwr_flag("GND", 22.86, 254.0)
    sch.pwr_flag("+5V", 35.56, 254.0)
    return sch


if __name__ == "__main__":
    write_project(build(), HERE, CUSTOM, "SENTINEL-UHF Clock & Timing Distribution")
